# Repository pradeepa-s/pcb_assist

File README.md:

# pcb_assist
Things to assist pcb development

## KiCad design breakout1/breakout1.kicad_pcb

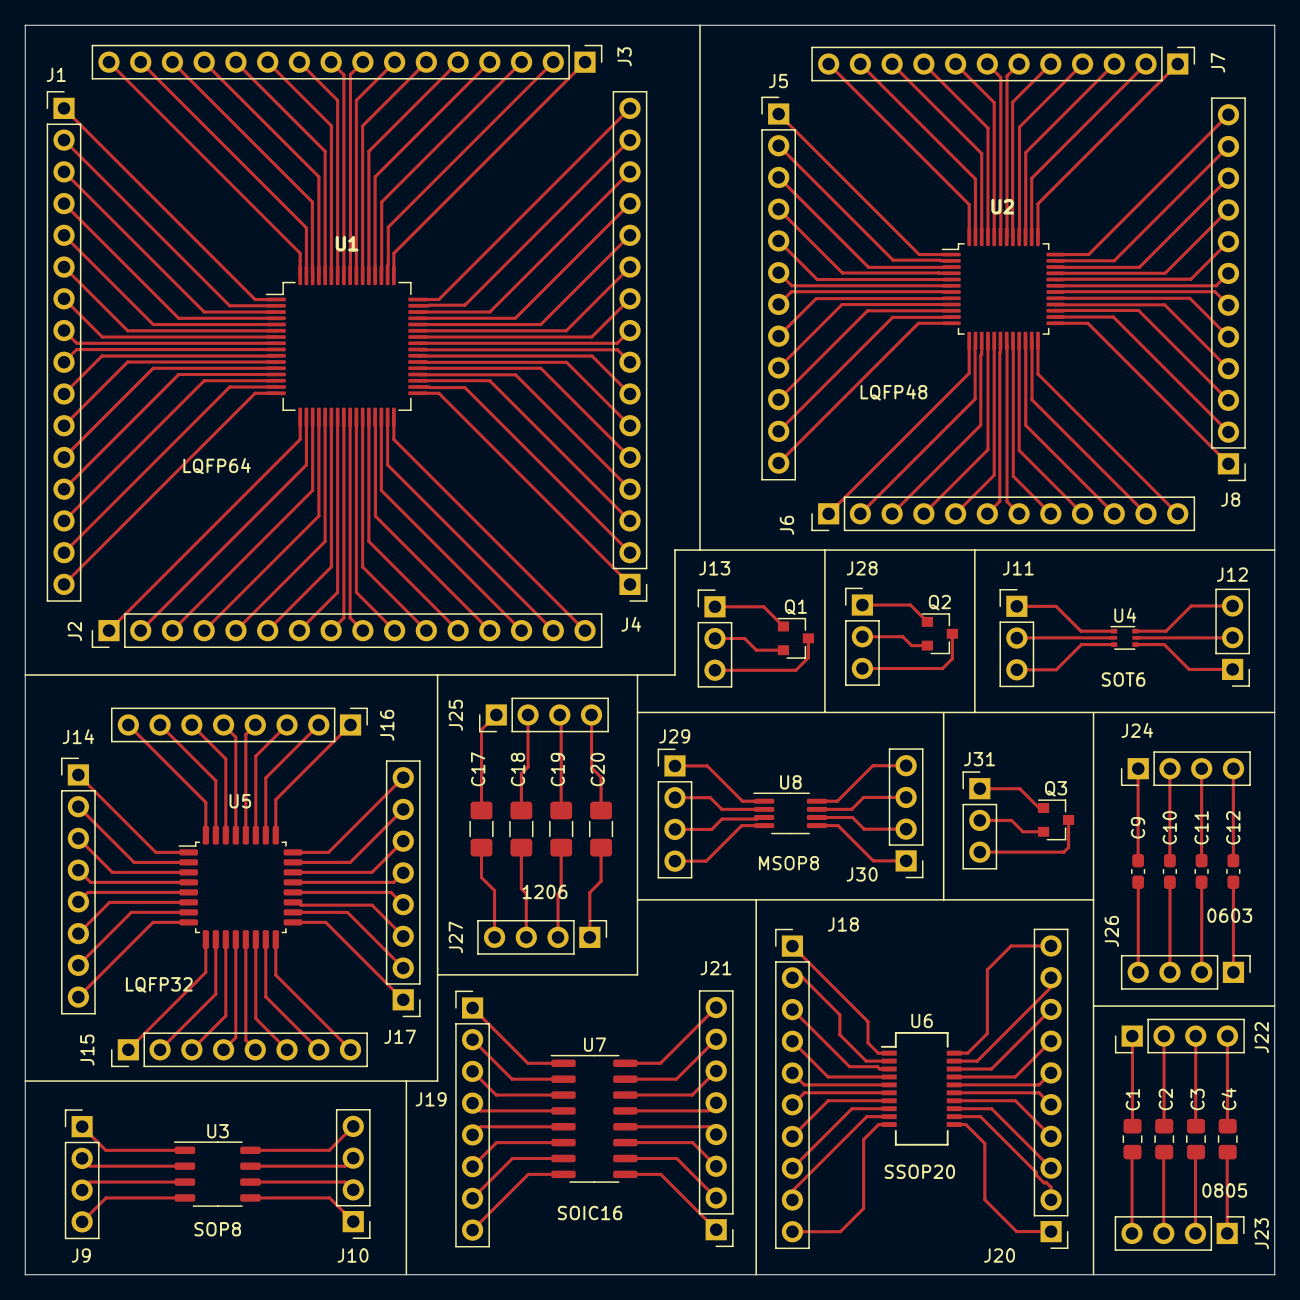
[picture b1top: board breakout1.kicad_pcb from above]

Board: 2 copper layers, 100.0 x 100.0 mm, 54 parts (0 on the bottom side), 235 nets.

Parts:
C1, C2, C3, C4: C_Small; C_0805_2012Metric_Pad1.18x1.45mm_HandSolder
C9, C10, C11, C12: C_Small; C_0603_1608Metric_Pad1.08x0.95mm_HandSolder
C17, C18, C19, C20: C_Small; C_1206_3216Metric_Pad1.42x1.75mm_HandSolder
J1, J2, J3, J4: Conn_01x16_Male; PinHeader_1x16_P2.54mm_Vertical
J5, J6, J7, J8: Conn_01x12_Male; PinHeader_1x12_P2.54mm_Vertical
J9, J10, J22, J23, J24, J25, J26, J27, J29, J30: Conn_01x04_Male; PinHeader_1x04_P2.54mm_Vertical
J11, J12, J13, J28, J31: Conn_01x03_Male; PinHeader_1x03_P2.54mm_Vertical
J14, J15, J16, J17, J19, J21: Conn_01x08_Male; PinHeader_1x08_P2.54mm_Vertical
J18, J20: Conn_01x10_Male; PinHeader_1x10_P2.54mm_Vertical
Q1, Q2, Q3: Q_NJFET_DGS; SOT-23
U1: ChipLQFP64; LQFP-64_10x10mm_P0.5mm
U2: ChipLQFP48; LQFP-48_7x7mm_P0.5mm
U3: ChipSOP8; SOP-8_3.9x4.9mm_P1.27mm
U4: Chip6SOT; SOT-666
U5: ChipLQFP32; LQFP-32_7x7mm_P0.8mm
U6: ChipSSOP20; SSOP-20_3.9x8.7mm_P0.635mm
U7: ChipSOIC16; SOIC-16_3.9x9.9mm_P1.27mm
U8: ChipMSOP8; MSOP-8_3x3mm_P0.65mm

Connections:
unnamed: C1.1, J23.4
unnamed: C1.2, J22.1
unnamed: C2.1, J23.3
unnamed: C2.2, J22.2
unnamed: C3.1, J23.2
unnamed: C3.2, J22.3
unnamed: C4.1, J23.1
unnamed: C4.2, J22.4
unnamed: C9.1, J26.4
unnamed: C9.2, J24.1
unnamed: C10.1, J26.3
unnamed: C10.2, J24.2
unnamed: C11.1, J26.2
unnamed: C11.2, J24.3
unnamed: C12.1, J26.1
unnamed: C12.2, J24.4
unnamed: C17.1, J27.4
unnamed: C17.2, J25.1
unnamed: C18.1, J27.3
unnamed: C18.2, J25.2
unnamed: C19.1, J27.2
unnamed: C19.2, J25.3
unnamed: C20.1, J27.1
unnamed: C20.2, J25.4
unnamed: J1.1, U1.1
unnamed: J1.2, U1.2
unnamed: J1.3, U1.3
unnamed: J1.4, U1.4
unnamed: J1.5, U1.5
unnamed: J1.6, U1.6
unnamed: J1.7, U1.7
unnamed: J1.8, U1.8
unnamed: J1.9, U1.9
unnamed: J1.10, U1.10
unnamed: J1.11, U1.11
unnamed: J1.12, U1.12
unnamed: J1.13, U1.13
unnamed: J1.14, U1.14
unnamed: J1.15, U1.15
unnamed: J1.16, U1.16
unnamed: J2.1, U1.17
unnamed: J2.2, U1.18
unnamed: J2.3, U1.19
unnamed: J2.4, U1.20
unnamed: J2.5, U1.21
unnamed: J2.6, U1.22
unnamed: J2.7, U1.23
unnamed: J2.8, U1.24
unnamed: J2.9, U1.25
unnamed: J2.10, U1.26
unnamed: J2.11, U1.27
unnamed: J2.12, U1.28
unnamed: J2.13, U1.29
unnamed: J2.14, U1.30
unnamed: J2.15, U1.31
unnamed: J2.16, U1.32
unnamed: J3.1, U1.49
unnamed: J3.2, U1.50
unnamed: J3.3, U1.51
unnamed: J3.4, U1.52
unnamed: J3.5, U1.53
unnamed: J3.6, U1.54
unnamed: J3.7, U1.55
unnamed: J3.8, U1.56
unnamed: J3.9, U1.57
unnamed: J3.10, U1.58
unnamed: J3.11, U1.59
unnamed: J3.12, U1.60
unnamed: J3.13, U1.61
unnamed: J3.14, U1.62
unnamed: J3.15, U1.63
unnamed: J3.16, U1.64
unnamed: J4.1, U1.33
unnamed: J4.2, U1.34
unnamed: J4.3, U1.35
unnamed: J4.4, U1.36
unnamed: J4.5, U1.37
unnamed: J4.6, U1.38
unnamed: J4.7, U1.39
unnamed: J4.8, U1.40
unnamed: J4.9, U1.41
unnamed: J4.10, U1.42
unnamed: J4.11, U1.43
unnamed: J4.12, U1.44
unnamed: J4.13, U1.45
unnamed: J4.14, U1.46
unnamed: J4.15, U1.47
unnamed: J4.16, U1.48
unnamed: J5.1, U2.1
unnamed: J5.2, U2.2
unnamed: J5.3, U2.3
unnamed: J5.4, U2.4
unnamed: J5.5, U2.5
unnamed: J5.6, U2.6
unnamed: J5.7, U2.7
unnamed: J5.8, U2.8
unnamed: J5.9, U2.9
unnamed: J5.10, U2.10
unnamed: J5.11, U2.11
unnamed: J5.12, U2.12
unnamed: J6.1, U2.13
unnamed: J6.2, U2.14
unnamed: J6.3, U2.15
unnamed: J6.4, U2.16
unnamed: J6.5, U2.17
unnamed: J6.6, U2.18
unnamed: J6.7, U2.19
unnamed: J6.8, U2.20
unnamed: J6.9, U2.21
unnamed: J6.10, U2.22
unnamed: J6.11, U2.23
unnamed: J6.12, U2.24
unnamed: J7.1, U2.37
unnamed: J7.2, U2.38
unnamed: J7.3, U2.39
unnamed: J7.4, U2.40
unnamed: J7.5, U2.41
unnamed: J7.6, U2.42
unnamed: J7.7, U2.43
unnamed: J7.8, U2.44
unnamed: J7.9, U2.45
unnamed: J7.10, U2.46
unnamed: J7.11, U2.47
unnamed: J7.12, U2.48
unnamed: J8.1, U2.25
unnamed: J8.2, U2.26
unnamed: J8.3, U2.27
unnamed: J8.4, U2.28
unnamed: J8.5, U2.29
unnamed: J8.6, U2.30
unnamed: J8.7, U2.31
unnamed: J8.8, U2.32
unnamed: J8.9, U2.33
unnamed: J8.10, U2.34
unnamed: J8.11, U2.35
unnamed: J8.12, U2.36
unnamed: J9.1, U3.1
unnamed: J9.2, U3.2
unnamed: J9.3, U3.3
unnamed: J9.4, U3.4
unnamed: J10.1, U3.5
unnamed: J10.2, U3.6
unnamed: J10.3, U3.7
unnamed: J10.4, U3.8
unnamed: J11.1, U4.1
unnamed: J11.2, U4.2
unnamed: J11.3, U4.3
unnamed: J12.1, U4.4
unnamed: J12.2, U4.5
unnamed: J12.3, U4.6
unnamed: J13.1, Q1.1
unnamed: J13.2, Q1.2
unnamed: J13.3, Q1.3
unnamed: J14.1, U5.1
unnamed: J14.2, U5.2
unnamed: J14.3, U5.3
unnamed: J14.4, U5.4
unnamed: J14.5, U5.5
unnamed: J14.6, U5.6
unnamed: J14.7, U5.7
unnamed: J14.8, U5.8
unnamed: J15.1, U5.9
unnamed: J15.2, U5.10
unnamed: J15.3, U5.11
unnamed: J15.4, U5.12
unnamed: J15.5, U5.13
unnamed: J15.6, U5.14
unnamed: J15.7, U5.15
unnamed: J15.8, U5.16
unnamed: J16.1, U5.25
unnamed: J16.2, U5.26
unnamed: J16.3, U5.27
unnamed: J16.4, U5.28
unnamed: J16.5, U5.29
unnamed: J16.6, U5.30
unnamed: J16.7, U5.31
unnamed: J16.8, U5.32
unnamed: J17.1, U5.17
unnamed: J17.2, U5.18
unnamed: J17.3, U5.19
unnamed: J17.4, U5.20
unnamed: J17.5, U5.21
unnamed: J17.6, U5.22
unnamed: J17.7, U5.23
unnamed: J17.8, U5.24
unnamed: J18.1, U6.1
unnamed: J18.2, U6.2
unnamed: J18.3, U6.3
unnamed: J18.4, U6.4
unnamed: J18.5, U6.5
unnamed: J18.6, U6.6
unnamed: J18.7, U6.7
unnamed: J18.8, U6.8
unnamed: J18.9, U6.9
unnamed: J18.10, U6.10
unnamed: J19.1, U7.1
unnamed: J19.2, U7.2
unnamed: J19.3, U7.3
unnamed: J19.4, U7.4
unnamed: J19.5, U7.5
unnamed: J19.6, U7.6
unnamed: J19.7, U7.7
unnamed: J19.8, U7.8
unnamed: J20.1, U6.11
unnamed: J20.2, U6.12
unnamed: J20.3, U6.13
unnamed: J20.4, U6.14
unnamed: J20.5, U6.15
unnamed: J20.6, U6.16
unnamed: J20.7, U6.17
unnamed: J20.8, U6.18
unnamed: J20.9, U6.19
unnamed: J20.10, U6.20
unnamed: J21.1, U7.9
unnamed: J21.2, U7.10
unnamed: J21.3, U7.11
unnamed: J21.4, U7.12
unnamed: J21.5, U7.13
unnamed: J21.6, U7.14
unnamed: J21.7, U7.15
unnamed: J21.8, U7.16
unnamed: J28.1, Q2.1
unnamed: J28.2, Q2.2
unnamed: J28.3, Q2.3
unnamed: J29.1, U8.1
unnamed: J29.2, U8.2
unnamed: J29.3, U8.3
unnamed: J29.4, U8.4
unnamed: J30.1, U8.5
unnamed: J30.2, U8.6
unnamed: J30.3, U8.7
unnamed: J30.4, U8.8
unnamed: J31.1, Q3.1
unnamed: J31.2, Q3.2
unnamed: J31.3, Q3.3

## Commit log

2021-07-22 Added the first breakout
